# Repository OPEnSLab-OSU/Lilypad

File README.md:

# Lilypad | [Wiki](https://github.com/OPEnSLab-OSU/Lilypad/wiki)
Project Lead: **Colin Hale-Brown**
Project Members: **Cameron Whitlow**, **Aiden Olsen**

Interested in the project? Email us at: halebroc@oregonstate.edu

The Lilypad is a floating water monitoring solution. It is able to measure water temperature, air temperature, humidity, and solar energy per square meter. It is designed to be easy to transport and deployed for at least 1 year at a time.

More information about assembly, testing, and operation can be found at the [wiki](https://github.com/OPEnSLab-OSU/Lilypad/wiki).

Ensure the 4G board has its switched in the Hardware and Shield orientations.

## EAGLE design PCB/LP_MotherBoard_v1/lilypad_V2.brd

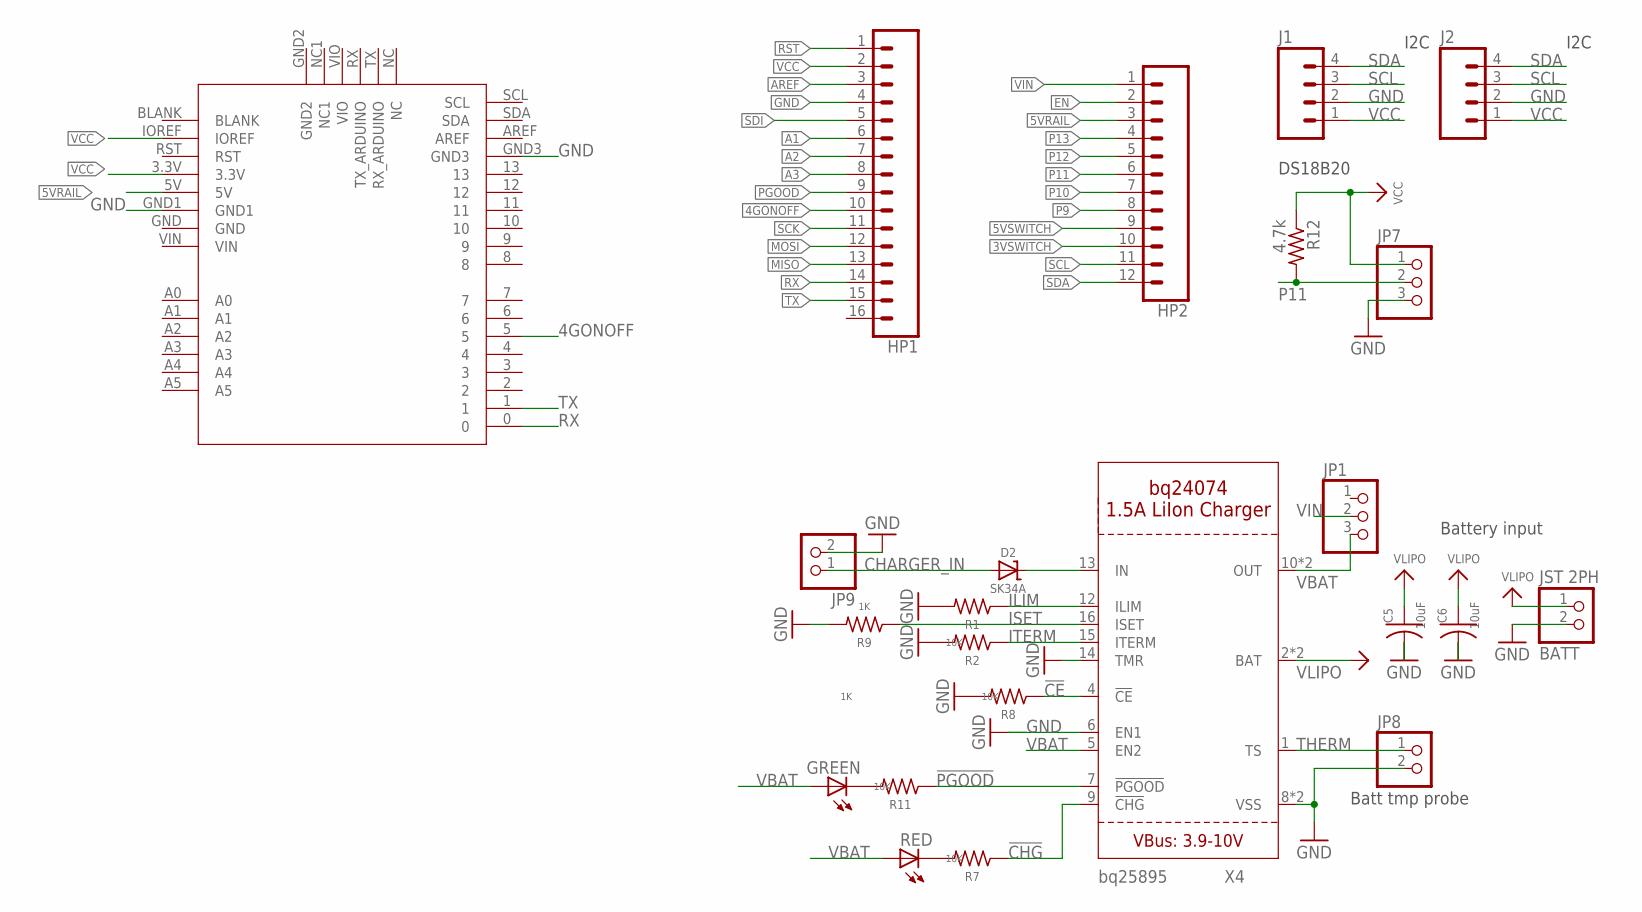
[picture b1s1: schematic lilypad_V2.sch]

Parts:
BATT: JST 2PH; JST-PH-2-SMT-RA
C5, C6: 10uF; C0805K
D2: SK34A; SMADIODE
GREEN: LEDSMT1206; 1206
HP1: CONN_16; 1X16
HP2: CONN_12; 1X12
J1, J2: M04PTH; 1X04
JP1, JP7: PINHD-1X3; 1X03
JP8, JP9: PINHD-1X2; 1X02
R1, R9: 1K; M0805
R2, R7, R8, R11: 10K; M0805
R12: 4.7k; 0805-THM
RED: LEDSMT1206; 1206
U$2: LTE_BOARD; LTE_BOARD_FOOTPRINT
X4: BQ24074; QFN16_3MM

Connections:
3VSWITCH: HP2.10
4GONOFF: HP1.10, U$2.5
5VRAIL: HP2.3, U$2.5V
5VSWITCH: HP2.9
!CE: R8.1, X4.4 (!CE)
!CHG: R7.1, X4.9 (!CHG)
!PGOOD: R11.1, X4.7 (!PGOOD)
A1: HP1.6
A2: HP1.7
A3: HP1.8
AREF: HP1.3
CHARGER_IN: D2.A, JP9.1
EN: HP2.2
GND: BATT.2 (1), C5.2, C6.2, HP1.4, J1.2, J2.2, JP7.3, JP8.2, JP9.2, R1.2, R2.2, R8.2, R9.2, U$2.GND1, U$2.GND3, X4.6 (EN1), X4.8 (VSS), X4.14 (TMR), X4.THERMAL (VSS)
ILIM: R1.1, X4.12 (ILIM)
ISET: R9.1, X4.16 (ISET)
ITERM: R2.1, X4.15 (ITERM)
MISO: HP1.13
MOSI: HP1.12
unnamed: GREEN.C, R11.2
unnamed: D2.C, X4.13 (IN)
unnamed: R7.2, RED.C
P9: HP2.8
P10: HP2.7
P11: HP2.6, JP7.2, R12.2
P12: HP2.5
P13: HP2.4
PGOOD: HP1.9
RST: HP1.1
RX: HP1.14, U$2.0
SCK: HP1.11
SCL: HP2.11, J1.3, J2.3
SDA: HP2.12, J1.4, J2.4
SDI: HP1.5
THERM: JP8.1, X4.1 (TS)
TX: HP1.15, U$2.1
VBAT: GREEN.A, JP1.3, RED.A, X4.5 (EN2), X4.10 (OUT), X4.11 (OUT)
VCC: HP1.2, J1.1, J2.1, JP7.1, R12.1, U$2.3.3V, U$2.IOREF
VIN: HP2.1, JP1.2
VLIPO: BATT.1 (2), C5.1, C6.1, X4.2 (BAT), X4.3 (BAT)

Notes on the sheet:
DS18B20
Batt tmp probe
Battery input
I2C

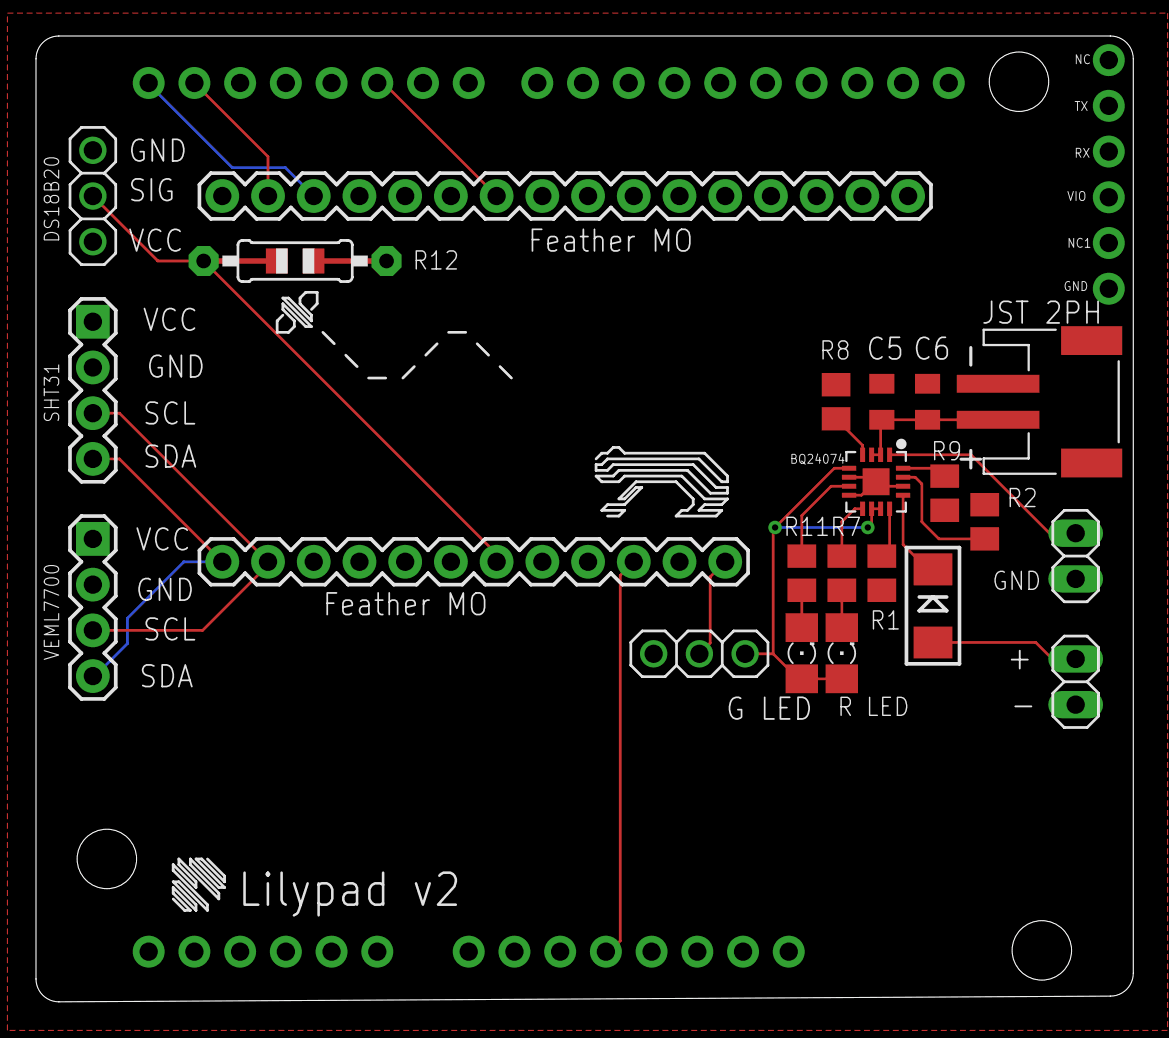
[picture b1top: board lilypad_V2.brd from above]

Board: 2 copper layers, 61.0 x 53.7 mm, 26 parts (1 on the bottom side), 23 nets.

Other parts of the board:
H1, H2, H3: STAND-OFF

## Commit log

2022-06-08 Add firmware
2022-10-20 Lilypad_V2 PCB First Revision
2022-10-20 Fixed some sch errors
2022-10-20 Lilypad PCB Post Review and README
2022-10-31 added SOP-8 package for INA169
2022-10-31 Updated shem/pcb w/ correct INA169 footprint
2022-10-31 added ignore
2022-12-03 added src code
2022-12-03 restructure
2022-12-03 better comments
2022-12-05 Update LilyPad4G.ino
    update to work with new temp sensor
2022-12-05 Update LilyPad4G.ino
    i changed it again
2022-12-06 working ds18b20
2022-12-09 conditional inclusion
2022-12-09 updated git ignore
2022-12-09 small change
2022-12-13 VEML7700 integration working
2022-12-13 cleaner code and comments
2023-01-12 update board schematic
2023-01-12 Update PCB
    Changed the wire connection type, adjusted for clearance. Fixed GND plane and moved the digital temp. sensor pin to 11.
2023-03-08 updated code
2023-03-08 added altered VEML Library
2023-03-09 added req's
2023-04-14 added VEML catch
2023-04-14 added assembly pics
2023-04-14 added DS_Store
2023-04-14 removed secrets file
2023-04-27 Github Organized for HardwareX and Delivery
2023-06-02 debug stuff
2023-06-02 pelican case assembly pics
2023-06-02 changed to png
2023-06-05 Content
2023-06-05 hypnos fix
2023-06-20 Update README.md
    fix tables not formatting properly. Didnt have headers set correctly.
2023-06-29 Converted images
2023-07-03 Updated software with additional librariers
2023-07-11 Updated required library info
2023-07-11 Updated software install instructions for ReadMet
2023-07-26 Added labeled to pcb
2023-07-26 Updated labels
2023-07-27 Finalized BOM table
2023-07-27 Added gerber file, template arduino secrets
2023-07-28 Replaced VEML mount with final
2023-08-09 Add checks for sensor init instead of while(1)

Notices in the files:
parts and their libraries:
SparkFun-Connectors: Licensing: Creative Commons ShareAlike 4.0 International - https://creativecommons.org/licenses/by-sa/4.0
